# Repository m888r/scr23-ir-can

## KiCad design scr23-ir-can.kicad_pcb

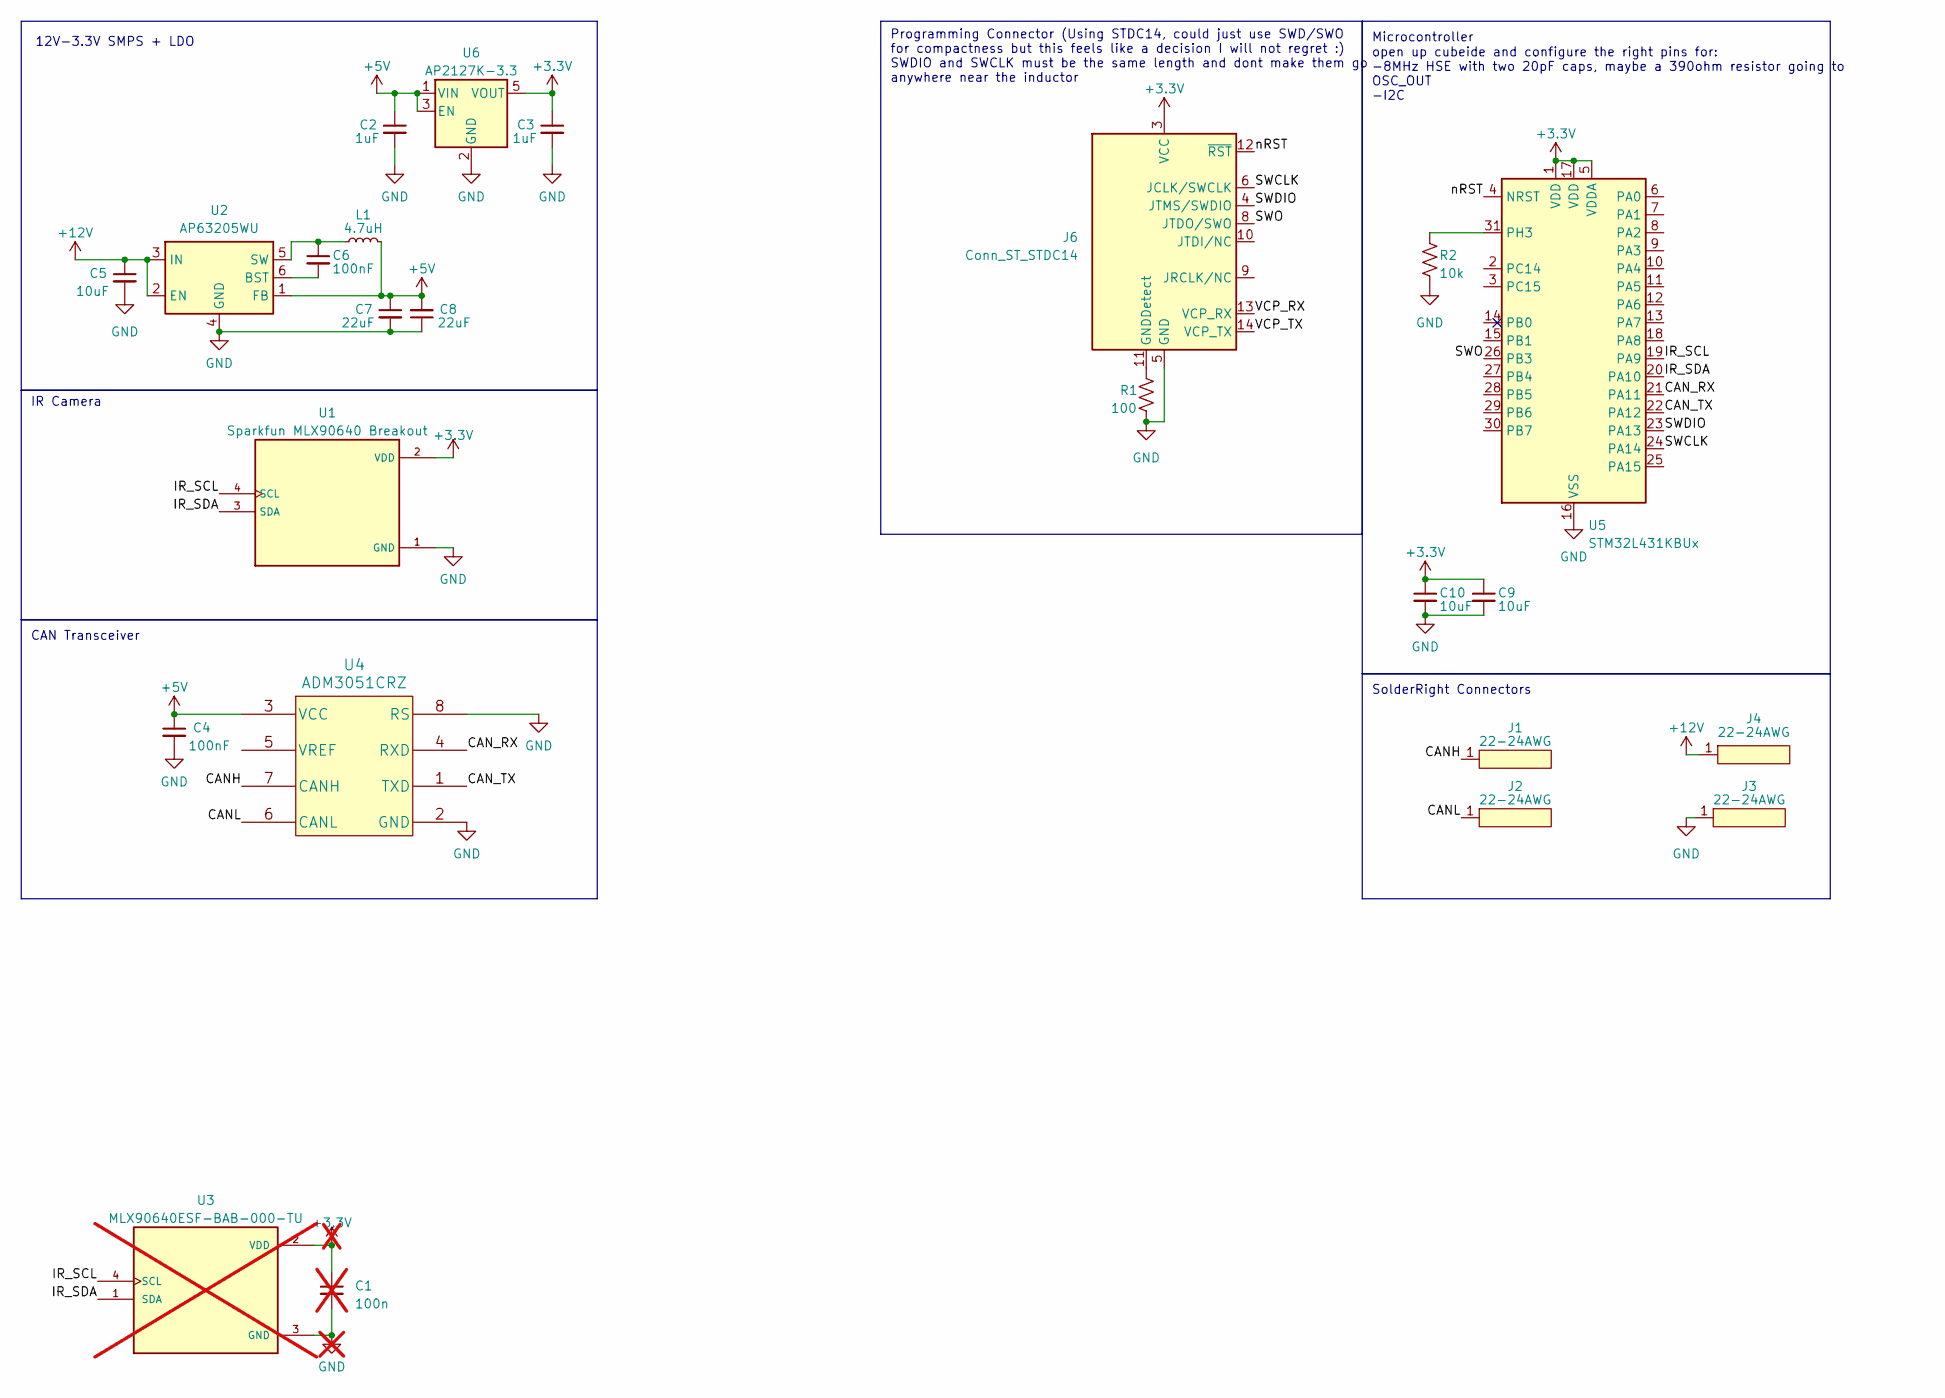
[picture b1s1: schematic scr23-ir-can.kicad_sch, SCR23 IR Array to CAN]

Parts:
C1: 100n; not fitted
C2, C3: 1uF; C_0603_1608Metric_Pad1.08x0.95mm_HandSolder
C4, C6: 100nF; C_0603_1608Metric_Pad1.08x0.95mm_HandSolder
C5, C9, C10: 10uF; C_0603_1608Metric_Pad1.08x0.95mm_HandSolder
C7, C8: 22uF; C_0603_1608Metric_Pad1.08x0.95mm_HandSolder
J1, J2, J3, J4: 22-24AWG; 1726770100
J6: Conn_ST_STDC14; PinHeader_2x07_P1.27mm_Horizontal
L1: 4.7uH; LQH44PH4R7MPRL
R1: 100; R_0603_1608Metric_Pad0.98x0.95mm_HandSolder
R2: 10k; R_0603_1608Metric_Pad0.98x0.95mm_HandSolder
U1: Sparkfun MLX90640 Breakout; MLX90640-Sparkfun-Breakout
U2: AP63205WU; TSOT-23-6
U3: MLX90640ESF-BAB-000-TU; TO-39-4; PARTREV 11; not fitted
U4: ADM3051CRZ; SOIC-8_3.9x4.9mm_P1.27mm
U5: STM32L431KBUx; QFN-32-1EP_5x5mm_P0.5mm_EP3.45x3.45mm
U6: AP2127K-3.3; SOT-23-5

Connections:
+3.3V: C1.1, C3.1, C9.1, C10.1, J6.3 (VCC), U1.2 (VDD), U3.2 (VDD), U5.1 (VDD), U5.5 (VDDA), U5.17 (VDD), U6.5 (VOUT)
+5V: C2.1, C4.1, C7.1, C8.2, L1.2, U2.1 (FB), U4.3 (VCC), U6.1 (VIN), U6.3 (EN)
+12V: C5.1, J4.1, U2.2 (EN), U2.3 (IN)
/CANH: J1.1, U4.7 (CANH)
/CANL: J2.1, U4.6 (CANL)
/CAN_RX: U4.4 (RXD), U5.21 (PA11)
/CAN_TX: U4.1 (TXD), U5.22 (PA12)
/IR_SCL: U1.4 (SCL), U3.4 (SCL), U5.19 (PA9)
/IR_SDA: U1.3 (SDA), U3.1 (SDA), U5.20 (PA10)
/SWCLK: J6.6 (JCLK/SWCLK), U5.24 (PA14)
/SWDIO: J6.4 (JTMS/SWDIO), U5.23 (PA13)
/SWO: J6.8 (JTDO/SWO), U5.26 (PB3)
/VCP_RX: J6.13 (VCP_RX)
/VCP_TX: J6.14 (VCP_TX)
/nRST: J6.12 (~RST), U5.4 (NRST)
GND: C1.2, C2.2, C3.2, C4.2, C5.2, C7.2, C8.1, C9.2, C10.2, J3.1, J6.5 (GND), J6.7 (GND), R1.2, R2.2, U1.1 (GND), U2.4 (GND), U3.3 (GND), U4.2 (GND), U4.8 (RS), U5.16 (VSS), U5.32 (VSS), U5.33 (VSS), U6.2 (GND)
unnamed: J6.11 (GNDDetect), R1.1
unnamed: C6.2, U2.6 (BST)
unnamed: C6.1, L1.1, U2.5 (SW)
unnamed: R2.1, U5.31 (PH3)

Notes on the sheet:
12V-3.3V SMPS + LDO
Programming Connector (Using STDC14, could just use SWD/SWO for compactness but this feels like a decision I will not regret :) SWDIO and SWCLK must be the same length and dont make them go anywhere near the inductor
SolderRight Connectors
Microcontroller
CAN Transceiver
open up cubeide and configure the right pins for: -8MHz HSE with two 20pF caps, maybe a 390ohm resistor going to OSC_OUT -I2C
IR Camera

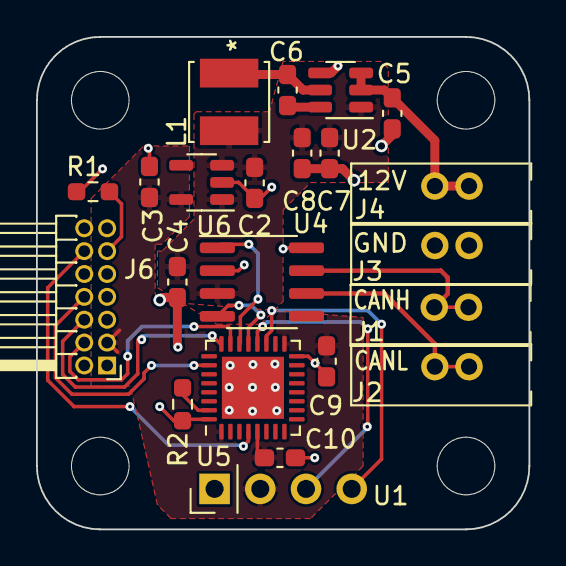
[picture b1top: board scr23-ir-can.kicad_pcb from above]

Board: 2 copper layers, 27.4 x 27.4 mm, 22 parts (0 on the bottom side), 18 nets.

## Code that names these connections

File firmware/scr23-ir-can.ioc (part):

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Mcu.Name=STM32L431K(B-C)Ux
Mcu.Package=UFQFPN32
Mcu.UserName=STM32L431KBUx
PA10.Mode=I2C
PA10.Signal=I2C1_SDA
PA11.Mode=CAN_Activate
PA11.Signal=CAN1_RX
PA12.Mode=CAN_Activate
PA12.Signal=CAN1_TX
PA13\ (JTMS-SWDIO).Mode=Trace_Asynchronous_SW
PA13\ (JTMS-SWDIO).Signal=SYS_JTMS-SWDIO
PA14\ (JTCK-SWCLK).Mode=Trace_Asynchronous_SW
PA14\ (JTCK-SWCLK).Signal=SYS_JTCK-SWCLK
PA9.Mode=I2C
PA9.Signal=I2C1_SCL
PB3\ (JTDO-TRACESWO).Mode=Trace_Asynchronous_SW
PB3\ (JTDO-TRACESWO).Signal=SYS_JTDO-SWO
RCC.HSE_VALUE=8000000
board=custom

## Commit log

2023-03-10 add all components, still need to do uC i2c connections and decoupling caps
2023-03-11 schematic done, added stdc14 programming connector
2023-03-11 add edge cuts
2023-03-11 added comment for maybe replacing the STDC14 thing
2023-03-12 add firmware project
2023-03-12 change to a through hole 2x7 for programming
2023-03-12 misc changes to layout, need to move everything to same layer
2023-03-13 better layout lol
2023-03-14 change programming boi to 1.27mm instead of 2.54, i had it wrong
2023-03-14 pcb finished
2023-03-14 ok NOW the pcb is done
2023-03-14 add labels to the solderright bois

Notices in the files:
parts and their libraries:
Copyright 2021 Accelerated Designs. All rights reserved.
